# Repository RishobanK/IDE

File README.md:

# nRF52840 BLE & CAN Sensor Hub

Production-grade edge telemetry firmware and hardware built for the **Nordic nRF52840 SoC** running **Zephyr RTOS**. Integrates environmental and inertial sensor telemetry published simultaneously over a custom **Bluetooth Low Energy (BLE 5.2)** GATT service and an **Industrial CAN 2.0B Bus Bridge**, secured by **MCUboot dual-bank Over-the-Air (OTA)** updates and verified through native **GitHub Actions CI**.

---

## 1. System Architecture & Concurrency Model

The firmware enforces clean task separation with preemptive priorities, lockless inter-thread queues, and non-blocking multi-protocol telemetry broadcasting.

```mermaid
graph TD
    subgraph Hardware_Peripherals [Hardware Sensors & Interfaces]
        BME280[Bosch BME280<br/>I2C1 @ 400kHz<br/>0x76]
        LSM6DSO[ST LSM6DSO IMU<br/>SPI1 @ 8MHz<br/>CS: P0.17 / P0.22]
        LED0[Status Heartbeat LED<br/>GPIO P0.13]
    end

    subgraph Zephyr_Kernel [Zephyr Real-Time Kernel]
        subgraph Thread_1 [Thread 1: Sensor Worker]
            T1_Desc[Priority: 5<br/>Period: 250 ms / 4 Hz<br/>Stack: 2048 B]
        end

        subgraph Inter_Thread [Inter-Thread IPC]
            MSGQ[s_sensor_msgq<br/>k_msgq FIFO Queue<br/>Depth: 16 items]
            MUTEX[s_sensor_mutex<br/>k_mutex<br/>Atomic Cache Lock]
        end

        subgraph Thread_2 [Thread 2: Telemetry & BLE Dispatcher]
            T2_Desc[Priority: 6<br/>Event-Driven<br/>Stack: 2048 B]
        end

        subgraph Thread_3 [Thread 3: Supervisor]
            T3_Desc[Priority: 7<br/>Period: 5000 ms<br/>Stack: 1024 B]
        end
    end

    subgraph Broadcast_Interfaces [Dual Telemetry Channels]
        GATT[BLE 5.2 GATT Service<br/>247-byte DLE Notify]
        CAN[CAN 2.0B Telemetry Bridge<br/>Frames 0x110, 0x111, 0x112]
    end

    %% Flow connections
    BME280 -->|TWIM1 DMA| T1_Desc
    LSM6DSO -->|SPIM1 DMA| T1_Desc
    T1_Desc -->|Enqueues Sample| MSGQ
    T1_Desc -->|Updates Cache| MUTEX

    MSGQ -->|k_msgq_get blocks| T2_Desc
    T2_Desc -->|GATT Notify| GATT
    T2_Desc -->|can_bridge_publish_telemetry| CAN

    T3_Desc -->|Flashes| LED0
    T3_Desc -->|Feeds WDT every 5s| WDT[Hardware Watchdog<br/>10s Timeout Window]
    T3_Desc -->|Monitors Stack Watermark| Thread_1
    T3_Desc -->|Monitors Stack Watermark| Thread_2
    T3_Desc -->|Confirms MCUboot Slot| MCUBOOT[MCUboot Bootloader<br/>Dual-Bank A/B Swap]
```

---

## 2. Industrial CAN 2.0B Telemetry Subsystem

The sensor hub acts as an edge bridge broadcasting real-time sensor metrics over an isolated CAN 2.0B network at 500 kbps.

```mermaid
flowchart LR
    HubNode["nRF52840 Sensor Hub<br/>(SocketCAN / Controller)"] -->|"CAN TX/RX"| Transceiver["CAN Transceiver<br/>(MCP2562 / TJA1051)"]
    Transceiver -->|"Differential Bus (CAN_H / CAN_L)"| CANBus[("CAN 2.0B Bus<br/>500 kbps, 120Ω Terminated")]
    CANBus --> PLC["Industrial PLC / Gateway"]
    CANBus --> Logger["CAN Logger / Telematics Unit"]
    CANBus --> Diagnostic["CANalyst-II / PC Tool"]
```

### CAN Frame Matrix (11-Bit Standard IDs)

All telemetry fields are packed in **Little-Endian (Intel)** format:

| Frame ID | DLC | Signal Name | Data Type | Units / Scaling Factor | Valid Range |
|:---:|:---:|---|:---:|:---:|:---:|
| **`0x110`** | 8 | Ambient Temperature | `int16_t` | $0.01\,^\circ\text{C}$ ($2500 \rightarrow 25.00\,^\circ\text{C}$) | $-40.00$ to $+85.00\,^\circ\text{C}$ |
| | | Relative Humidity | `uint16_t` | $0.01\,\%\,\text{RH}$ ($5500 \rightarrow 55.00\,\%\,\text{RH}$) | $0.00$ to $100.00\,\%\,\text{RH}$ |
| | | Barometric Pressure | `uint32_t` | $1\,\text{Pa}$ ($101325 \rightarrow 101325\,\text{Pa}$) | $30000$ to $110000\,\text{Pa}$ |
| **`0x111`** | 6 | Acceleration X | `int16_t` | $1\,\text{mg}$ | $\pm 2000\,\text{mg}$ / $\pm 4000\,\text{mg}$ |
| | | Acceleration Y | `int16_t` | $1\,\text{mg}$ | $\pm 2000\,\text{mg}$ / $\pm 4000\,\text{mg}$ |
| | | Acceleration Z | `int16_t` | $1\,\text{mg}$ | $\pm 2000\,\text{mg}$ / $\pm 4000\,\text{mg}$ |
| **`0x112`** | 6 | Angular Velocity X | `int16_t` | $1\,\text{mdps}$ ($0.001\,^\circ/\text{s}$) | $\pm 2000^\circ/\text{s}$ |
| | | Angular Velocity Y | `int16_t` | $1\,\text{mdps}$ ($0.001\,^\circ/\text{s}$) | $\pm 2000^\circ/\text{s}$ |
| | | Angular Velocity Z | `int16_t` | $1\,\text{mdps}$ ($0.001\,^\circ/\text{s}$) | $\pm 2000^\circ/\text{s}$ |

> **Non-blocking Guarantee:** Transmissions use `can_send(..., K_MSEC(100), ...)` so bus-off conditions or missing acks never block real-time RTOS scheduling.

---

## 3. Hardware SMT & Native KiCad 8/9 Deliverables

Complete production hardware designs are located under [`hardware/`](hardware/):
- **KiCad Project:** [`hardware/nrf52840_sensor_hub.kicad_pro`](hardware/nrf52840_sensor_hub.kicad_pro)
- **Schematic:** [`hardware/nrf52840_sensor_hub.kicad_sch`](hardware/nrf52840_sensor_hub.kicad_sch)
- **4-Layer PCB:** [`hardware/nrf52840_sensor_hub.kicad_pcb`](hardware/nrf52840_sensor_hub.kicad_pcb)
- **Engineering Specification:** [`hardware/HARDWARE_SPEC.md`](hardware/HARDWARE_SPEC.md)
- **Assembly SMT BOM:** [`hardware/bom_jlcpcb.csv`](hardware/bom_jlcpcb.csv)

### 4-Layer PCB Stackup Specifications
- **Layer 1 (F.Cu - 1.0 oz / 35 µm):** High-speed RF GCPW transmission line, digital buses, SMT component pads.
- **Layer 2 (In1.Cu - 0.5 oz / 17.5 µm):** Solid, unbroken Ground Reference Plane.
- **Layer 3 (In2.Cu - 0.5 oz / 17.5 µm):** Power Distribution Plane (`+3V3`, `V_BATT`, `VBUS`).
- **Layer 4 (B.Cu - 1.0 oz / 35 µm):** Low-speed control routing and bottom ground pour.
- **Form Factor:** Compact $50\,\text{mm} \times 35\,\text{mm}$ enclosure footprint with $8.5 \times 5.5\,\text{mm}$ 4-layer antenna keepout zone.

### Power Management Topology
```
USB-C 5V (J2) ──► Microchip MCP73831T (U4) ──► 3.7V LiPo (J3) ──► TI TPS7A2033 (U5) ──► +3V3 System Rail
                  (500mA Fast-Charge, 4.2V)                       (Ultra-Low IQ=6.5µA, 300mA)
```

---

## 4. Hardware Pinout Table

| Peripheral | Signal / Function | nRF52840 Pin | Physical Connection | Electrical Details |
|---|---|---|---|---|
| **Bosch BME280** | I2C1 SDA | **P0.26** | U2 Pin 3 (SDI) | 3.3V, 4.7kΩ pull-up to +3V3 |
| **Bosch BME280** | I2C1 SCL | **P0.27** | U2 Pin 4 (SCK) | 3.3V, 4.7kΩ pull-up to +3V3 |
| **ST LSM6DSO** | SPI1 SCK | **P0.19** / P0.31 | U3 Pin 3 (SPC) | 8 MHz max, Mode 3 (CPOL=1, CPHA=1) |
| **ST LSM6DSO** | SPI1 MOSI | **P0.20** / P0.30 | U3 Pin 2 (SDI) | 3.3V push-pull |
| **ST LSM6DSO** | SPI1 MISO | **P0.21** / P0.29 | U3 Pin 1 (SDO) | 3.3V input |
| **ST LSM6DSO** | SPI1 CS | **P0.22** / P0.17 | U3 Pin 4 (CS) | Active-low GPIO chip-select |
| **ST LSM6DSO** | Data Ready INT | **P0.18** / P0.19 | U3 Pin 5 (INT1) | Active-high rising-edge interrupt |
| **Status LED** | LED1 Heartbeat | **P0.13** | D1 (Green 0603) | Active-low, 5s supervisor toggle |
| **BLE Activity** | LED2 Connect | **P0.14** | D2 (Red 0603) | Active-low, set on connect |
| **SWD Debug** | SWDIO / SWDCLK | SWD Pins | J1 (FTSH-105-01) | Standard 10-pin 1.27mm Cortex debug |
| **USB-C PHY** | VBUS / CC1 / CC2| USB-C Port | J2 (16-Pin Receptacle)| 5.1kΩ pull-downs on CC1/CC2 |

---

## 5. Directory Layout

```
.
├── .github/workflows/
│   └── firmware_ci.yml         # GitHub Actions CI/CD (native test + Cppcheck)
├── app/
│   ├── CMakeLists.txt          # Zephyr application CMake definition
│   ├── prj.conf                # Zephyr Kconfig subsystem flags
│   ├── app.overlay             # Devicetree overlay (I2C1 & SPI1 buses)
│   └── src/
│       ├── main.c              # Thread spawning, queues, supervisor
│       ├── sensor_manager.c    # Sensor bus acquisition and caching
│       ├── ble_service.c       # Custom GATT service, advertising, notify
│       ├── can_bridge.c        # Industrial CAN 2.0B telemetry bridge
│       ├── crash_logger.c      # NVS persistent diagnostic breadcrumbs
│       └── ota_manager.c       # MCUboot self-test and confirmation logic
├── boards/arm/custom_sensor_node/
│   ├── custom_sensor_node.dts  # Full Device Tree: I2C1, SPI1, partitions
│   ├── custom_sensor_node-pinctrl.dtsi # Pin mux states (active + sleep)
│   └── custom_sensor_node_defconfig    # Minimum Kconfig fragment
├── hardware/
│   ├── nrf52840_sensor_hub.kicad_pro   # KiCad 8/9 Project configuration
│   ├── nrf52840_sensor_hub.kicad_sch   # KiCad 8/9 Schematic (clean sub-unit S-expressions)
│   ├── nrf52840_sensor_hub.kicad_pcb   # KiCad 8/9 4-Layer PCB layout
│   ├── HARDWARE_SPEC.md        # Comprehensive schematic & manufacturing spec
│   └── bom_jlcpcb.csv          # Automated JLCPCB / PCBWay SMT BOM
├── include/
│   ├── sensor_manager.h        # Sensor structures & IPC queue headers
│   ├── ble_service.h           # GATT UUIDs and configuration structs
│   ├── can_bridge.h            # CAN 2.0B frame definitions and API
│   ├── crash_logger.h          # NVS crash logging interface
│   └── ota_manager.h           # Bootloader lifecycle interface
├── tests/
│   └── test_sensor_ringbuf.c   # Unit tests for queue boundary and FIFO
├── build_and_sign.sh           # Automated build, imgtool signing, and packaging
├── TECHNICAL_SUMMARY.md        # Deep architectural and quantifiable metrics
└── README.md                   # Project overview and quickstart guide
```

---

## 6. Quickstart: Build & Execution Instructions

### Prerequisites
- [nRF Connect SDK v2.6.x](https://developer.nordicsemi.com/nRF_Connect_SDK/doc/latest/nrf/installation.html) or Zephyr RTOS v3.5+
- `west` meta-tool (`pip install west`)
- GNU Arm Embedded Toolchain (`arm-zephyr-eabi`)
- Segger J-Link Tools (`nrfjprog` or `JLinkExe`)

### 1. Build for the Custom Production Board (`west build`)
```bash
# Initialize and fetch dependencies
west init -l app
west update

# Compile for custom production sensor node
west build -b custom_sensor_node app -d build
```

### 2. Flash to Target Hardware via Segger J-Link
```bash
west flash -d build
```

### 3. Real-Time Debug Logging via Segger RTT
```bash
JLinkRTTViewer --device NRF52840_XXAA --interface SWD --speed 4000
```

### 4. Automated Signing & MCUboot OTA Image Generation
```bash
chmod +x build_and_sign.sh
./build_and_sign.sh custom_sensor_node 1.0.0
# Outputs signed binary ready for OTA: build/zephyr/zephyr.signed.bin
```

---

## 7. Unit Testing & CI/CD Pipeline

Host-native unit tests run on developer workstations or in continuous integration without hardware dependencies:

### Running Unit Tests Locally
```bash
gcc -Wall -Wextra -O2 tests/test_sensor_ringbuf.c -o test_ringbuf
./test_ringbuf
```

Expected Output:
```
Running sensor_ringbuf unit tests...
  [PASS] test_ringbuf_empty_initial_state
  [PASS] test_ringbuf_fifo_ordering
  [PASS] test_ringbuf_overrun_drop_oldest
All 3 unit tests passed successfully!
```

### Automated GitHub Actions CI Matrix
The workflow in `.github/workflows/firmware_ci.yml` executes on every push/PR to `main` and `master`:
- **Native Unit Test Job:** Compiles and runs test suites using host GCC in $<10\,\text{seconds}$.
- **Cppcheck Static Analysis:** Scans `app/src/` for memory leaks, undefined behavior, and style defects in $<15\,\text{seconds}$.

---

## 8. License
This project is licensed under the Apache 2.0 License. See [LICENSE](LICENSE) for details.

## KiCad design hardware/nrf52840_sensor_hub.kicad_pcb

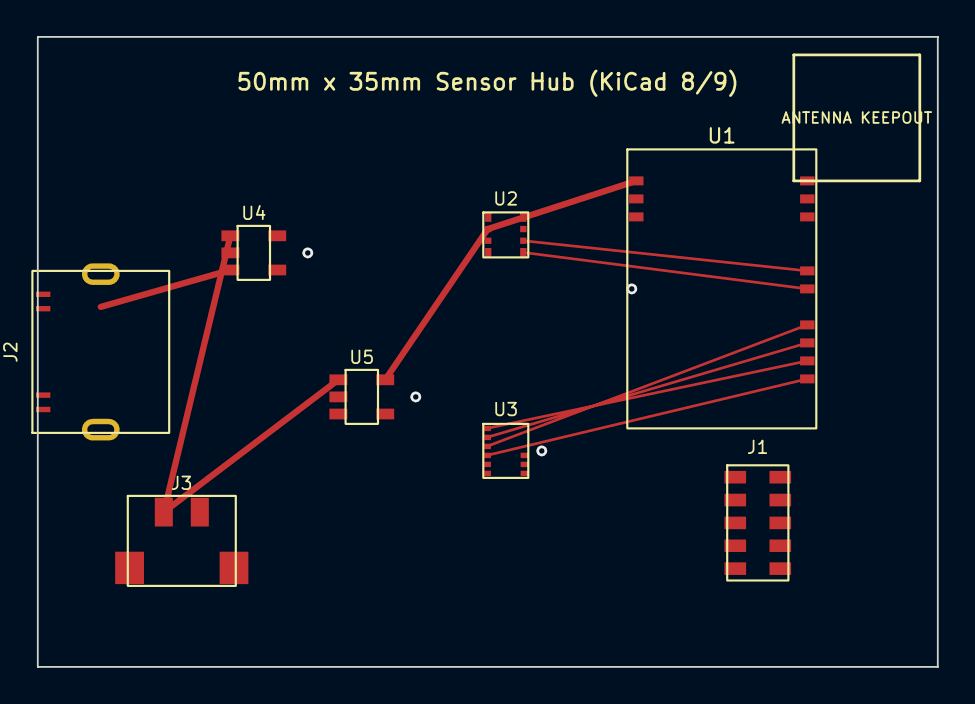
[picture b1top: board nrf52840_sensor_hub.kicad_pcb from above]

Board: 4 copper layers, 50.0 x 35.0 mm, 8 parts (0 on the bottom side), 10 nets.

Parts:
J1: SWD_10P; PinHeader_2x05_P1.27mm_Vertical_SMD
J2: TYPE-C-16P; USB_C_Receptacle_HRO_TYPE-C-31-M-12
J3: JST-PH-2P; JST_PH_B2B-PH-SM4-TB_1x02-1MP_P2.00mm_Vertical
U1: Raytac MDBT50Q-1M; Raytac_MDBT50Q-1M
U2: BME280; Bosch_LGA-8_2.5x2.5mm_P0.65mm_ClockwisePinNumbering
U3: LSM6DSO; LGA-14_2.5x3mm_P0.5mm_LayoutBorder1x6
U4: MCP73831T; SOT-23-5
U5: TPS7A2033; SOT-23-5

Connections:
+3V3: J1.1, U1.1, U1.2, U2.2, U2.6, U2.8, U3.8, U3.9, U5.5
GND: J1.3, J1.5, J1.9, J2.A1, J2.B12, J2.SH1, J2.SH2, J3.2, J3.MP1, J3.MP2, U1.3, U2.1, U2.5, U2.7, U3.6, U3.7, U4.2, U4.5, U5.2
I2C_SCL: U1.8, U2.4
I2C_SDA: U1.7, U2.3
SPI_CS: U1.12, U3.4
SPI_MISO: U1.11, U3.1
SPI_MOSI: U1.10, U3.2
SPI_SCK: U1.9, U3.3
VBUS: J2.A4, J2.B9, U4.4
V_BATT: J3.1, U4.3, U5.1, U5.3

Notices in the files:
README.md:
License: Apache 2.0
